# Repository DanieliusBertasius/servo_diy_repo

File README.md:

Note to self: add ground test points in upcoming projects

<br>
PSU:

<br>
MCU:

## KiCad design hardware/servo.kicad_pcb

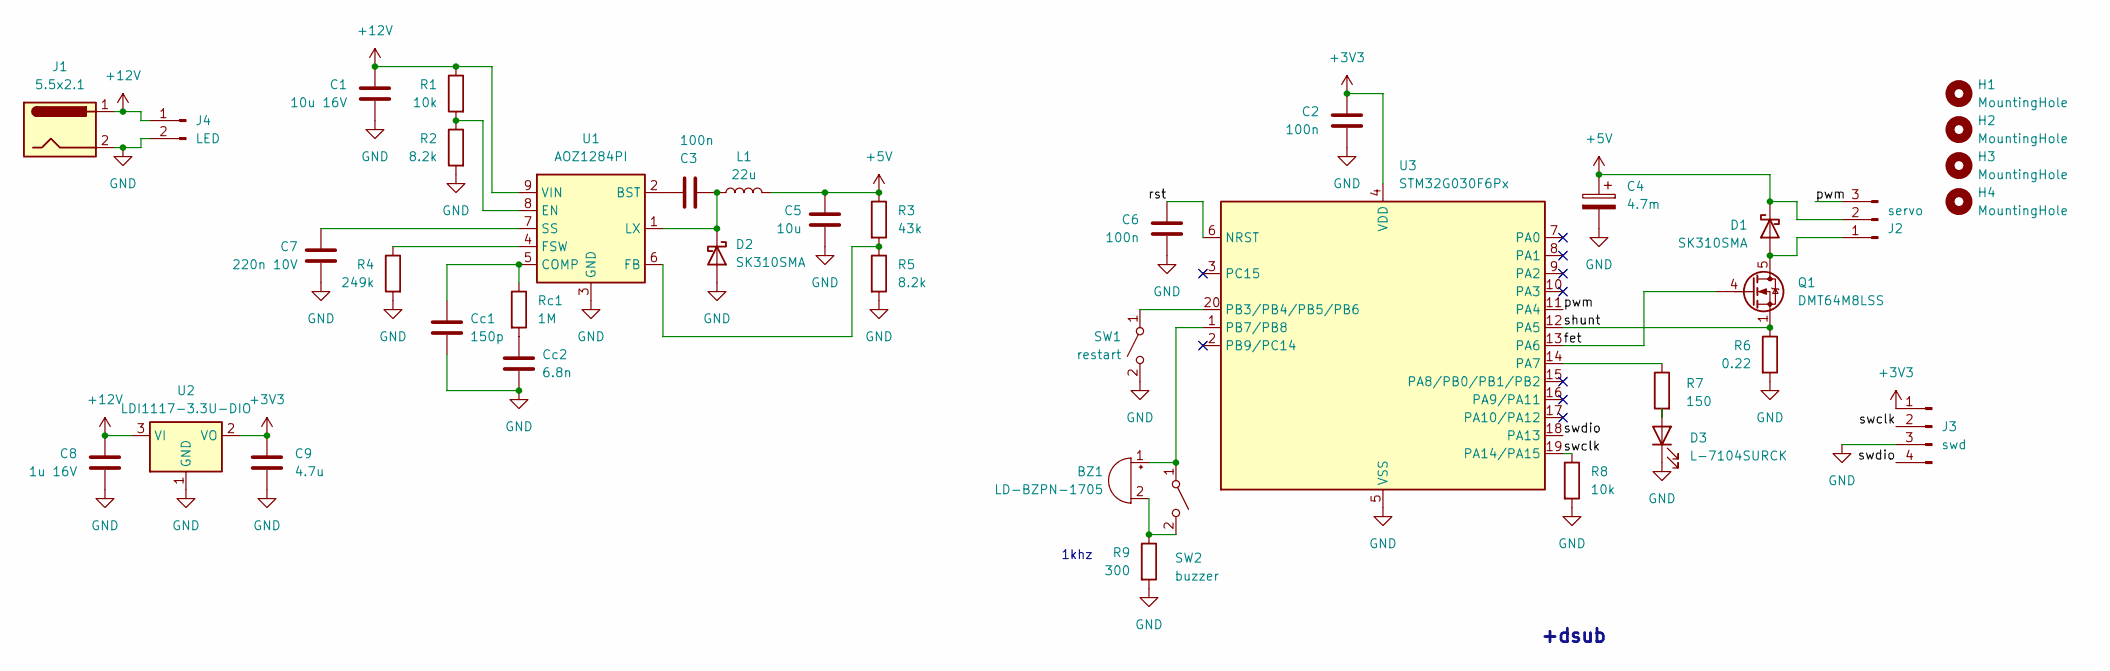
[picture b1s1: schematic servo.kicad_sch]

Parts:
BZ1: LD-BZPN-1705; LOUDITY LD-BZPN-1705
C1: 10u 16V; C_0805_2012Metric_Pad1.18x1.45mm_HandSolder
C2, C3, C6: 100n; C_0805_2012Metric_Pad1.18x1.45mm_HandSolder
C4: 4.7m; CP_Radial_D16.0mm_P7.50mm
C5: 10u; C_0805_2012Metric_Pad1.18x1.45mm_HandSolder
C7: 220n 10V; C_0805_2012Metric_Pad1.18x1.45mm_HandSolder
C8: 1u 16V; C_0805_2012Metric_Pad1.18x1.45mm_HandSolder
C9: 4.7u; C_0805_2012Metric_Pad1.18x1.45mm_HandSolder
Cc1: 150p; C_0805_2012Metric_Pad1.18x1.45mm_HandSolder
Cc2: 6.8n; C_0805_2012Metric_Pad1.18x1.45mm_HandSolder
D1, D2: SK310SMA; D_SMA_Handsoldering
D3: L-7104SURCK; LED_D3.0mm
H1, H2, H3, H4: MountingHole; MountingHole_3.2mm_M3_DIN965_Pad_TopOnly
J1: 5.5x2.1; BarrelJack_diy
J2: servo; PinHeader_1x03_P2.54mm_Vertical
J3: swd; PinHeader_1x04_P2.54mm_Vertical
J4: LED; PhoenixContact_MSTBA_2,5_2-G-5,08_1x02_P5.08mm_Horizontal
L1: 22u; LD2-HV
Q1: DMT64M8LSS; SOIC-8_3.9x4.9mm_P1.27mm
R1, R8: 10k; R_0805_2012Metric_Pad1.20x1.40mm_HandSolder
R2, R5: 8.2k; R_0805_2012Metric_Pad1.20x1.40mm_HandSolder
R3: 43k; R_0805_2012Metric_Pad1.20x1.40mm_HandSolder
R4: 249k; R_0805_2012Metric_Pad1.20x1.40mm_HandSolder
R6: 0.22; R_0805_2012Metric_Pad1.20x1.40mm_HandSolder
R7: 150; R_0805_2012Metric_Pad1.20x1.40mm_HandSolder
R9: 300; R_0805_2012Metric_Pad1.20x1.40mm_HandSolder
Rc1: 1M; R_0805_2012Metric_Pad1.20x1.40mm_HandSolder
SW1: restart; SolderWire-0.25sqmm_1x02_P4.2mm_D0.65mm_OD1.7mm
SW2: buzzer; SolderWire-0.25sqmm_1x02_P4.2mm_D0.65mm_OD1.7mm
U1: AOZ1284PI; SOIC-8-1EP_3.9x4.9mm_P1.27mm_EP2.29x3mm_diy
U2: LDI1117-3.3U-DIO; SOT-89-3_Handsoldering
U3: STM32G030F6Px; TSSOP-20_4.4x6.5mm_P0.65mm

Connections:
+3V3: C2.1, C9.1, J3.1, U2.2 (VO), U3.4 (VDD)
+5V: C4.1, C5.1, D1.1 (K), J2.2, L1.2, R3.1
+12V: C1.1, C8.1, J1.1, J4.1, R1.1, U1.9 (VIN), U2.3 (VI)
/fet: Q1.4 (G), U3.13 (PA6)
/pwm: J2.3, U3.11 (PA4)
/rst: C6.1, U3.6 (NRST)
/shunt: Q1.1 (S), Q1.2 (S), Q1.3 (S), R6.1, U3.12 (PA5)
/swclk: J3.2, R8.1, U3.19 (PA14/PA15)
/swdio: J3.4, U3.18 (PA13)
GND: C1.2, C2.2, C4.2, C5.2, C6.2, C7.2, C8.2, C9.2, Cc1.2, Cc2.2, D2.2 (A), D3.1 (K), J1.2, J3.3, J4.2, R2.2, R4.2, R5.2, R6.2, R8.2, R9.2, SW1.2 (B), U1.3 (GND), U2.1 (GND), U3.5 (VSS)
unnamed: BZ1.1 (+), SW2.1 (A), U3.1 (PB7/PB8)
unnamed: BZ1.2 (-), R9.1, SW2.2 (B)
unnamed: Cc2.1, Rc1.2
unnamed: D1.2 (A), J2.1, Q1.5 (D), Q1.6 (D), Q1.7 (D), Q1.8 (D)
unnamed: C3.2, D2.1 (K), L1.1, U1.1 (LX)
unnamed: D3.2 (A), R7.2
unnamed: SW1.1 (A), U3.20 (PB3/PB4/PB5/PB6)
unnamed: C3.1, U1.2 (BST)
unnamed: Cc1.1, Rc1.1, U1.5 (COMP)
unnamed: R1.2, R2.1, U1.8 (EN)
unnamed: R3.2, R5.1, U1.6 (FB)
unnamed: R4.1, U1.4 (FSW)
unnamed: C7.1, U1.7 (SS)
unnamed: R7.1, U3.14 (PA7)

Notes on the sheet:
1khz
+dsub

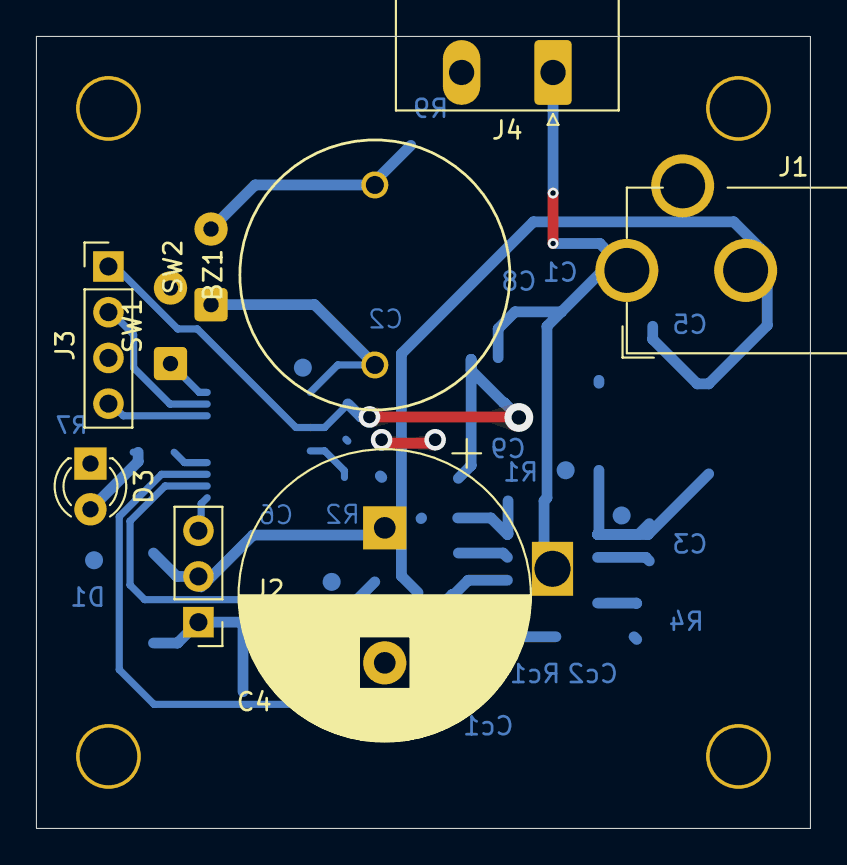
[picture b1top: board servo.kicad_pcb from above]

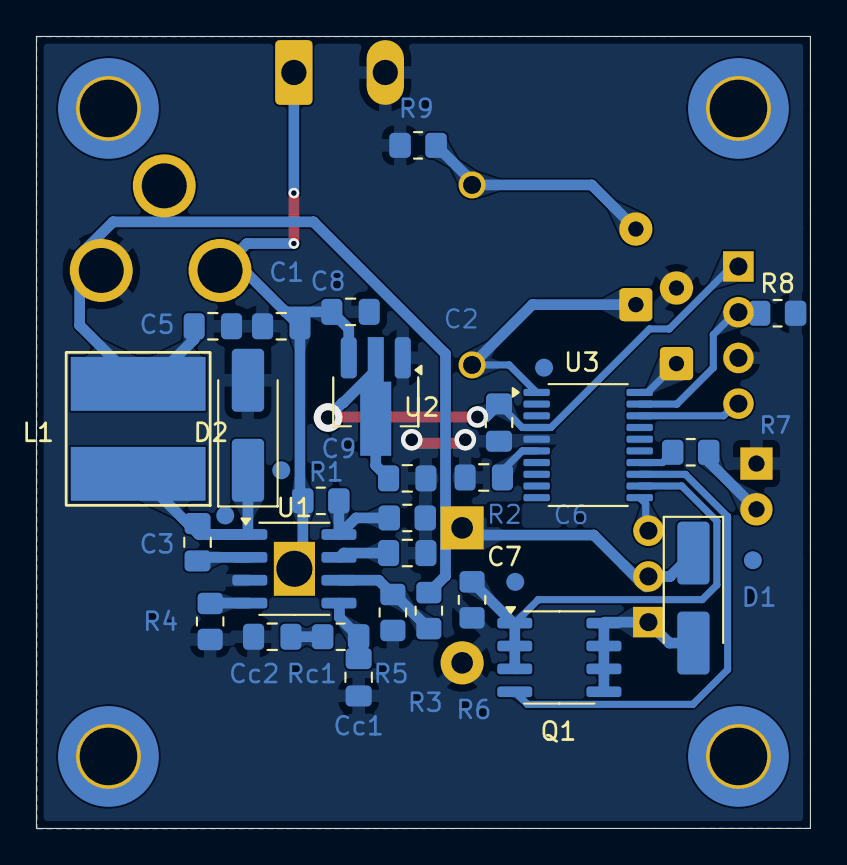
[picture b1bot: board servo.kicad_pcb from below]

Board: 2 copper layers, 43.0 x 44.0 mm, 40 parts (31 on the bottom side), 24 nets.

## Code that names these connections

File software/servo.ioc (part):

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Mcu.Name=STM32G030F6Px
Mcu.Package=TSSOP20
Mcu.UserName=STM32G030F6Px
PA13.Mode=Serial_Wire
PA13.Signal=SYS_SWDIO
PA14-BOOT0.Mode=Serial_Wire
PA14-BOOT0.Signal=SYS_SWCLK
PA14-BOOT0__PA15.StandardMode=true
PA4.Signal=S_TIM14_CH1
PA5.Mode=IN5
PA5.Signal=ADC1_IN5
PA6.GPIOParameters=GPIO_Label
PA6.GPIO_Label=fet
PA6.Signal=GPIO_Output
PA7.GPIOParameters=GPIO_Label
PA7.GPIO_Label=led
PA7.Signal=GPIO_Output
PB0__PB1__PB2__PA8.StandardMode=true
PB3.GPIOParameters=GPIO_PuPd,GPIO_ModeDefaultEXTI
PB3.GPIO_ModeDefaultEXTI=GPIO_MODE_IT_FALLING
PB3.GPIO_PuPd=GPIO_PULLUP
PB3.Signal=GPXTI3
PB3__PB4__PB5__PB6.StandardMode=true
PB7.GPIOParameters=GPIO_Label
PB7.GPIO_Label=buzzer
PB7.Signal=GPIO_Output
PB7__PB8.StandardMode=true
PC14-OSC32_IN\ (PC14)__PB9.StandardMode=true
RCC.HSE_VALUE=8000000
RCC.SYSCLKFreq_VALUE=64000000
RCC.SYSCLKSource=RCC_SYSCLKSOURCE_PLLCLK
board=custom
